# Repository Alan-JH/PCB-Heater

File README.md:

# PCB-Heater

Solder reflow hotplate design based on Carl Bugeja's idea and proof of concept.

Aluminum PCB as the resistive heating element, 200x200mm. Control board is separated and has displays for time and temperature (target and actual), and an SD card to read reflow profiles and save data to. Runs off of 3.3V logic and the ATTiny1614/1624 MCU. Input voltage (for the heating element) can range up to around 50V by design (Plan to use 36-48V), and the element itself should have a resistance of 5.1Ohm at 25C. Target maximum temperature is around 200C. Optional cooling provided by a 5V fan.

v1.0 results: 215C max temperature, 25 to 200C in around 4 minutes. 5 ohm resistance at room temperature, 10 ohm at 200C

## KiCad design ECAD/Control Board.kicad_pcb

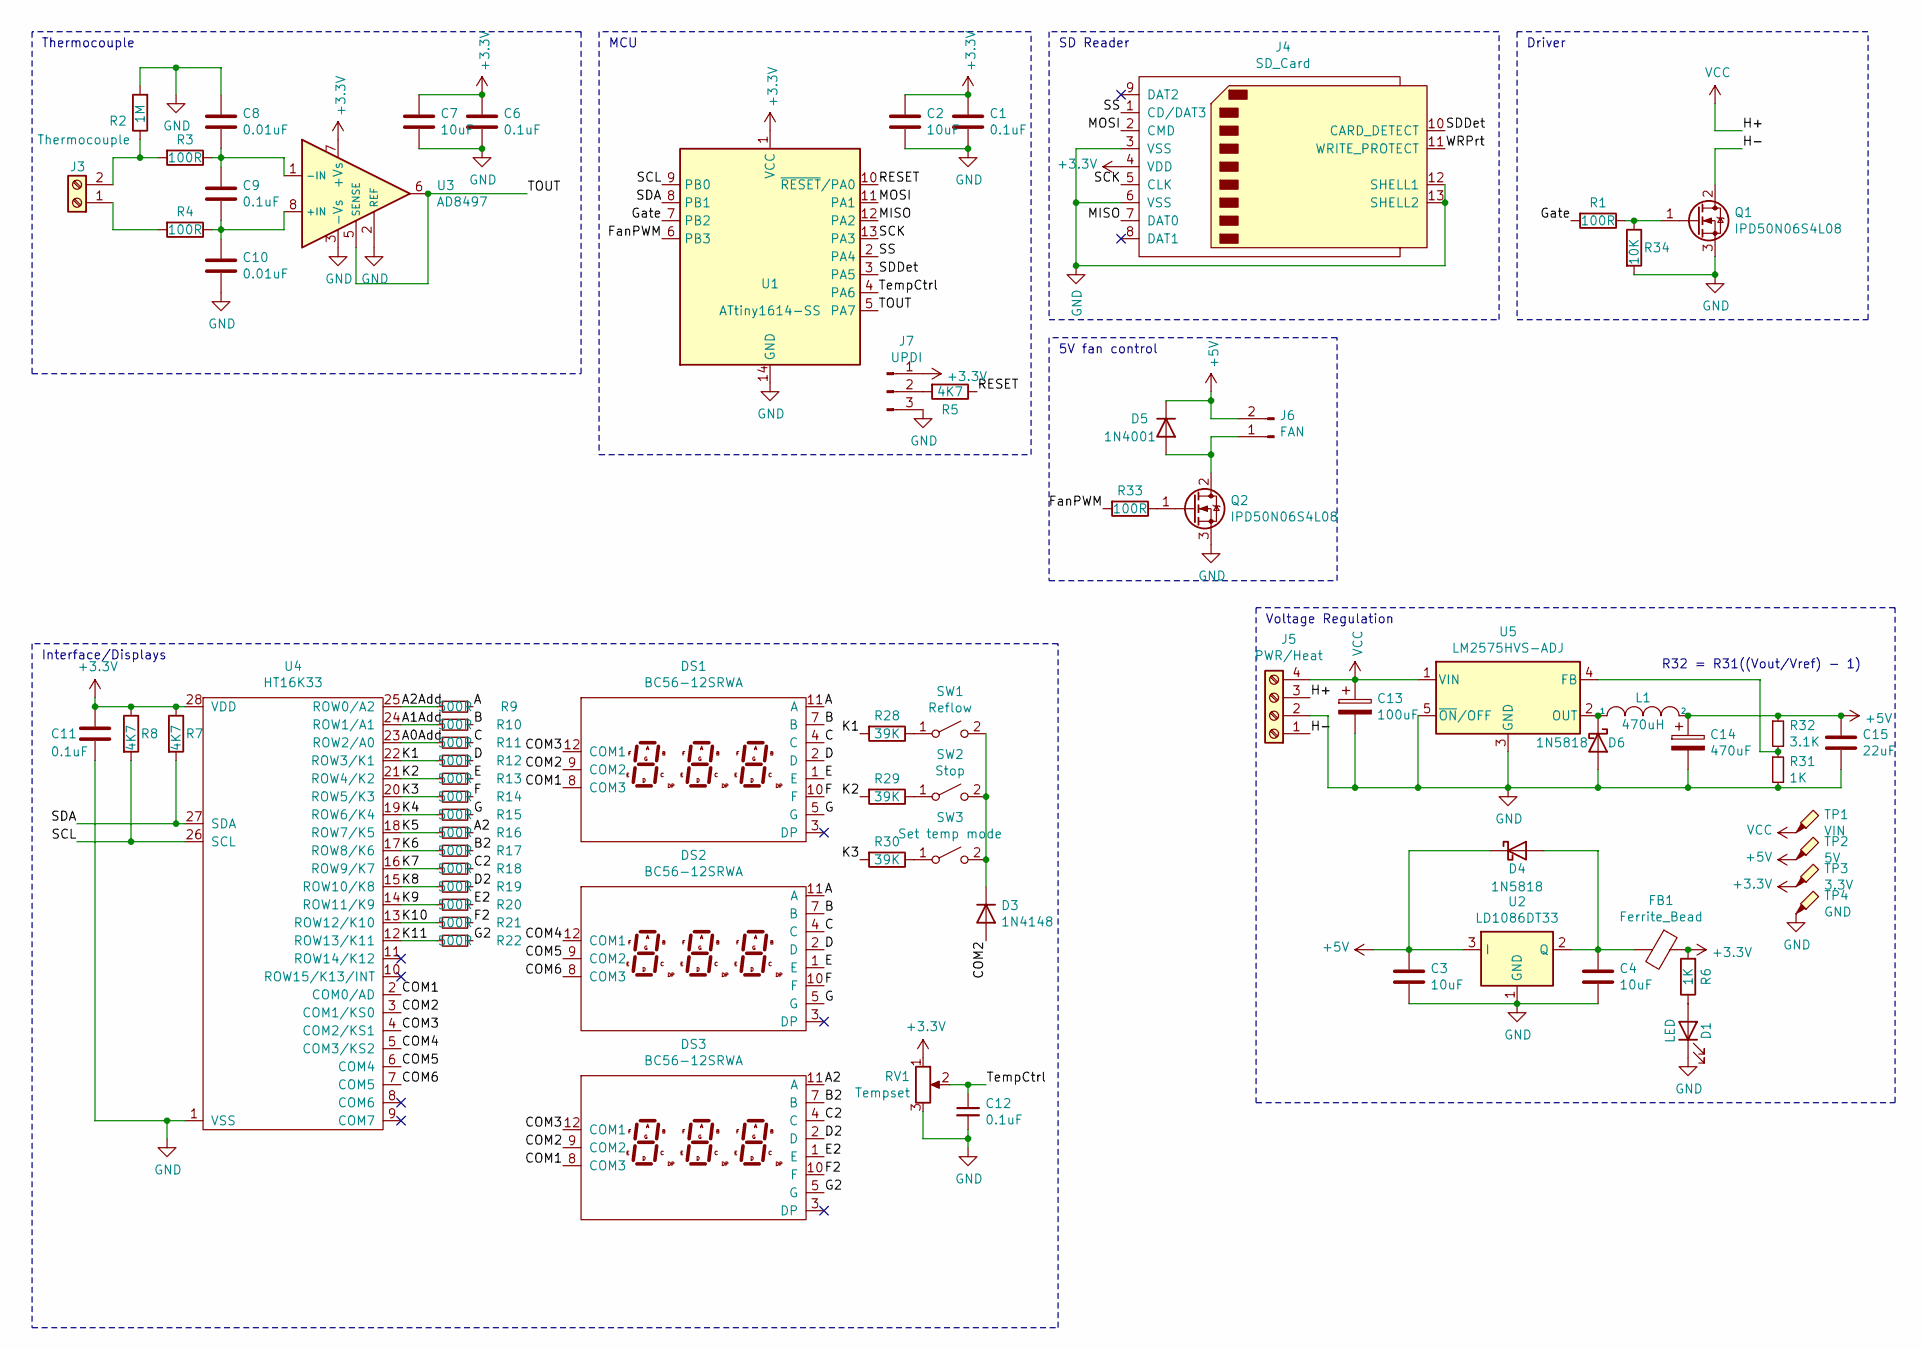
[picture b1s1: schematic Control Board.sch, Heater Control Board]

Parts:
C1, C6, C9, C11, C12: 0.1uF; C_0805_2012Metric_Pad1.18x1.45mm_HandSolder
C2, C3, C4, C7: 10uF; C_0805_2012Metric_Pad1.18x1.45mm_HandSolder
C8, C10: 0.01uF; C_0805_2012Metric_Pad1.18x1.45mm_HandSolder
C13: 100uF; CP_Elec_10x10.5
C14: 470uF; CP_Elec_8x10.5
C15: 22uF; C_0805_2012Metric_Pad1.18x1.45mm_HandSolder
D1: LED; LED_0805_2012Metric_Pad1.15x1.40mm_HandSolder
D3: 1N4148; D_0805_2012Metric_Pad1.15x1.40mm_HandSolder
D4, D6: 1N5818; D_T-1_P5.08mm_Horizontal
D5: 1N4001; D_T-1_P5.08mm_Horizontal
DS1, DS2, DS3: BC56-12SRWA
FB1: Ferrite_Bead; R_0805_2012Metric_Pad1.20x1.40mm_HandSolder
J3: Thermocouple; CUI-TB006-508-02BE
J4: SD_Card; SD_TE_2041021
J5: PWR/Heat; Molex-38711-2204
J6: FAN; PinHeader_1x02_P2.54mm_Vertical
J7: UPDI; PinHeader_1x03_P2.54mm_Vertical
L1: 470uH; L_12x12mm_H8mm
Q1, Q2: IPD50N06S4L08; TO-252-2
R1, R3, R4, R33: 100R; R_1206_3216Metric_Pad1.30x1.75mm_HandSolder
R2: 1M; R_1206_3216Metric_Pad1.30x1.75mm_HandSolder
R5, R7, R8: 4K7; R_1206_3216Metric_Pad1.30x1.75mm_HandSolder
R6: 1K; R_1206_3216Metric_Pad1.30x1.75mm_HandSolder
R9, R10, R11, R12, R13, R14, R15, R16, R17, R18, R19, R20, R21, R22: 500R; R_0805_2012Metric_Pad1.20x1.40mm_HandSolder
R28, R29, R30: 39K; R_1206_3216Metric_Pad1.30x1.75mm_HandSolder
R31: 1K; R_0805_2012Metric_Pad1.20x1.40mm_HandSolder
R32: 3.1K; R_0805_2012Metric_Pad1.20x1.40mm_HandSolder
R34: 10K; R_1206_3216Metric_Pad1.30x1.75mm_HandSolder
RV1: Tempset; PinHeader_1x03_P2.54mm_Vertical
SW1: Reflow; SW_PUSH_6mm_H7.3mm
SW2: Stop; SW_PUSH_6mm_H7.3mm
SW3: Set temp mode; SW_PUSH_6mm_H7.3mm
TP1: VIN; TestPoint_Pad_2.0x2.0mm
TP2: 5V; TestPoint_Pad_2.0x2.0mm
TP3: 3.3V; TestPoint_Pad_2.0x2.0mm
TP4: GND; TestPoint_Pad_2.0x2.0mm
U1: ATtiny1614-SS; SOIC-14_3.9x8.7mm_P1.27mm
U2: LD1086DT33; TO-252-3_TabPin2
U3: AD8497; MSOP-8_3x3mm_P0.65mm
U4: HT16K33; Holtek-HT16K33-SOP28-0
U5: LM2575HVS-ADJ; TO-263-5_TabPin3

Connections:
+3V3: C1.1, C2.1, C6.1, C7.1, C11.1, FB1.1, J4.4 (VDD), J7.1, R6.2, R7.1, R8.1, RV1.1, TP3.1, U1.1 (VCC), U3.7 (+Vs), U4.28 (VDD)
+5V: C3.1, C14.1, C15.1, D4.1 (K), D5.1 (K), J6.2, L1.2, R32.1, TP2.1, U2.3 (I)
/A: DS1.11 (A), DS2.11 (A), R9.1
/A0Add: R11.2, U4.23 (ROW2/A0)
/A1Add: R10.2, U4.24 (ROW1/A1)
/A2: DS3.11 (A), R16.1
/A2Add: R9.2, U4.25 (ROW0/A2)
/B: DS1.7 (B), DS2.7 (B), R10.1
/B2: DS3.7 (B), R17.1
/C: DS1.4 (C), DS2.4 (C), R11.1
/C2: DS3.4 (C), R18.1
/COM1: DS1.8 (COM3), DS3.8 (COM3), U4.2 (COM0/AD)
/COM2: D3.2 (A), DS1.9 (COM2), DS3.9 (COM2), U4.3 (COM1/KS0)
/COM3: DS1.12 (COM1), DS3.12 (COM1), U4.4 (COM2/KS1)
/COM4: DS2.12 (COM1), U4.5 (COM3/KS2)
/COM5: DS2.9 (COM2), U4.6 (COM4)
/COM6: DS2.8 (COM3), U4.7 (COM5)
/D: DS1.2 (D), DS2.2 (D), R12.1
/D2: DS3.2 (D), R19.1
/E: DS1.1 (E), DS2.1 (E), R13.1
/E2: DS3.1 (E), R20.1
/F: DS1.10 (F), DS2.10 (F), R14.1
/F2: DS3.10 (F), R21.1
/FanPWM: R33.2, U1.6 (PB3)
/G: DS1.5 (G), DS2.5 (G), R15.1
/G2: DS3.5 (G), R22.1
/Gate: R1.2, U1.7 (PB2)
/H-: J5.1, Q1.2 (D)
/K1: R12.2, R28.2, U4.22 (ROW3/K1)
/K2: R13.2, R29.2, U4.21 (ROW4/K2)
/K3: R14.2, R30.2, U4.20 (ROW5/K3)
/K4: R15.2, U4.19 (ROW6/K4)
/K5: R16.2, U4.18 (ROW7/K5)
/K6: R17.2, U4.17 (ROW8/K6)
/K7: R18.2, U4.16 (ROW9/K7)
/K8: R19.2, U4.15 (ROW10/K8)
/K9: R20.2, U4.14 (ROW11/K9)
/K10: R21.2, U4.13 (ROW12/K10)
/K11: R22.2, U4.12 (ROW13/K11)
/MISO: J4.7 (DAT0), U1.12 (PA2)
/MOSI: J4.2 (CMD), U1.11 (PA1)
/RESET: R5.1, U1.10 (~RESET~/PA0)
/SCK: J4.5 (CLK), U1.13 (PA3)
/SCL: R8.2, U1.9 (PB0), U4.26 (SCL)
/SDA: R7.2, U1.8 (PB1), U4.27 (SDA)
/SDDet: J4.10 (CARD_DETECT), U1.3 (PA5)
/SS: J4.1 (CD/DAT3), U1.2 (PA4)
/TOUT: U1.5 (PA7), U3.5 (SENSE), U3.6
/TempCtrl: C12.1, RV1.2, U1.4 (PA6)
GND: C1.2, C2.2, C3.2, C4.2, C6.2, C7.2, C8.1, C10.2, C11.2, C12.2, C13.2, C14.2, C15.2, D1.1 (K), D6.2 (A), J4.3 (VSS), J4.6 (VSS), J4.12 (SHELL1), J4.13 (SHELL2), J5.2, J7.3, Q1.3 (S), Q2.3 (S), R2.2, R31.2, R34.2, RV1.3, TP4.1, U1.14 (GND), U2.1 (GND), U3.2 (REF), U3.3 (-Vs), U4.1 (VSS), U5.3 (GND), U5.5 (~ON~/OFF)
unnamed: C4.1, D4.2 (A), FB1.2, U2.2 (Q)
unnamed: C8.2, C9.1, R3.1, U3.1 (-IN)
unnamed: C9.2, C10.1, R4.1, U3.8 (+IN)
unnamed: D1.2 (A), R6.1
unnamed: D3.1 (K), SW1.2 (B), SW2.2 (B), SW3.2 (B)
unnamed: D5.2 (A), J6.1, Q2.2 (D)
unnamed: D6.1 (K), L1.1, U5.2 (OUT)
unnamed: J3.1, R4.2
unnamed: J3.2, R2.1, R3.2
unnamed: J7.2, R5.2
unnamed: Q1.1 (G), R1.1, R34.1
unnamed: Q2.1 (G), R33.1
unnamed: R28.1, SW1.1 (A)
unnamed: R29.1, SW2.1 (A)
unnamed: R30.1, SW3.1 (A)
unnamed: R31.1, R32.2, U5.4 (FB)
VCC: C13.1, J5.3, J5.4, TP1.1, U5.1 (VIN)

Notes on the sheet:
Thermocouple
Driver
SD Reader
Interface/Displays
MCU
5V fan control
R32 = R31((Vout/Vref) - 1)
Voltage Regulation

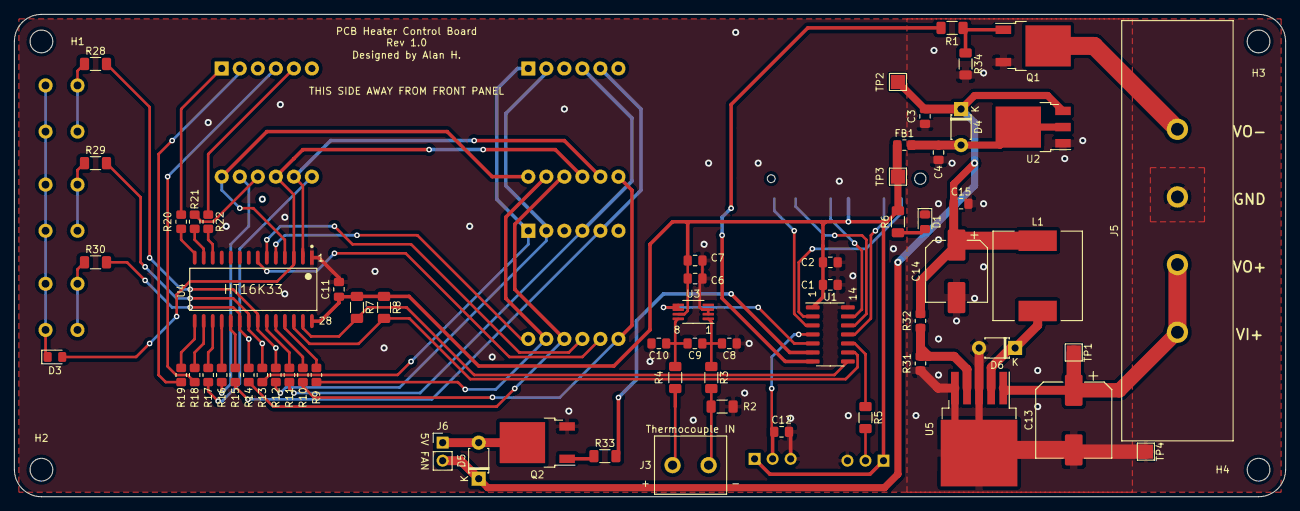
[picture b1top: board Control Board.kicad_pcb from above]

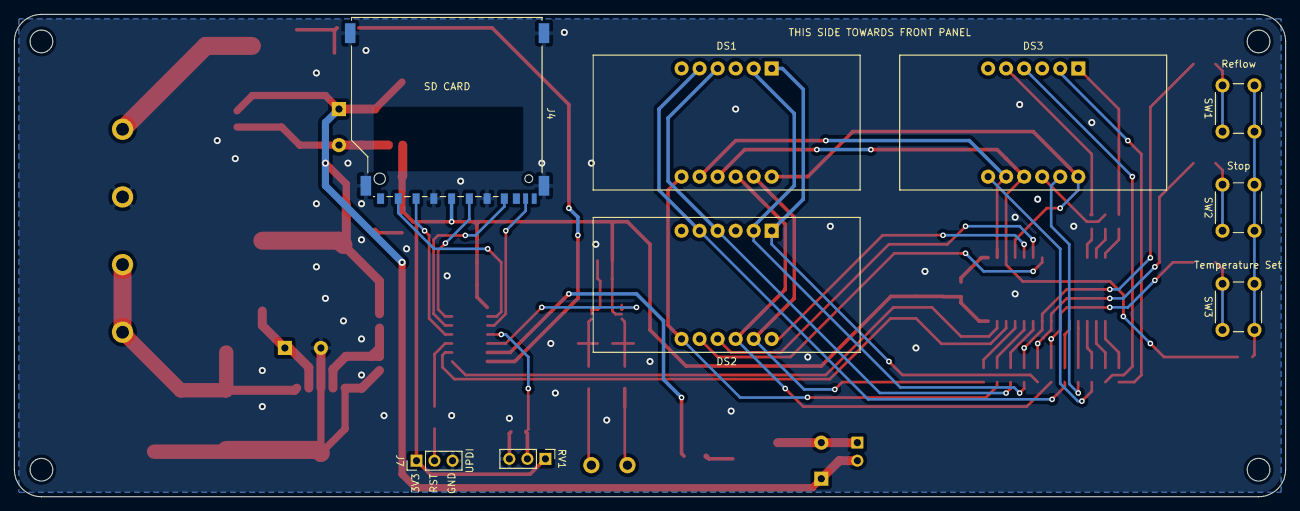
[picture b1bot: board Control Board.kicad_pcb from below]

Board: 2 copper layers, 179.1 x 67.9 mm, 77 parts (9 on the bottom side), 67 nets.

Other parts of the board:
H1, H2, H3, H4: MountingHole_3.2mm_M3

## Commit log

2021-09-07 Cleanup
    Renamed files, removed temp files
2021-09-07 Re-associated libraries
2021-09-07 Perforate Heatbed
    Added a grid of 2.1mm holes, which may help thermal performance.
2021-09-09 Widened traces to 30mil
    In order to reduce resistance and increase wattage, traces widened up to 30mil (theoretical 5.4R at 25C)
2021-09-09 High voltage modifications
    Widened high voltage tracks and replaced schottky diode with higher back voltage diode.
2021-09-10 Revised control board schematic
    Replaced single LDO setup with cascaded LDOs, so that a higher input voltage can be used, and the intermediate 12V can be used to power a fan. Added the appropriate circuitry to control a fan. Added 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
    Layout is still to be updated
2021-09-10 Added footprints to board
2021-09-10 Revert "Perforated heater"
2021-09-10 Revert "Merge pull request #3 from Alan-JH/revert-2-Perforated-Heater"
    This reverts commit 4dedab5329d0c4c589ebeff6f2ce44676f29a142, reversing
    changes made to 18337d37710a704d8d57a7691b9b75f48685949f.
2021-09-10 Update heater silkscreen info
2021-09-11 Re-arrange components
2021-09-11 Added pulldown to mosfet gate
2021-09-13 Replaced primary LDO with LM317
2021-09-14 Replaced linear regulator with switching regulator
    Chose switching regulator for the sake of less heat. Undecided as to whether I will end up using a premade module or incorporating the circuitry
    Replaced 12V rail with 5V rail, to increase efficiency of the LDO. Requires a 5V fan now.
    Bumped revision number to 0.4
2021-09-14 Remove extra LC filter, replace with ceramic cap
2021-09-15 Associate footprints and update board
2021-09-16 Lay out switching regulator
    Also reshuffling the SD card and power port placements
2021-09-16 More routing
2021-09-19 Routed V0.4 Control Board
    Finished routing board, removed ununsed models and footprints, re-exported gerbers and .STEP files
2021-09-20 BOM Export, minor via edits and gerber re-export
2021-10-08 start fixing errors in board
2021-10-09 Finish rerouting LDO
2021-10-10 Fix major silkscreen error, push to rev0.5
2021-10-11 Fix thermocouple + and - pins
2021-10-12 Firmware: implement PID
2021-10-12 Widen heater tracks
    reduce actual resistance from 7ohm to 5ohm
2021-10-12 attempt to fix pid
2021-10-12 clean up code
2021-10-12 more comments in firmware
2021-10-12 firmware
2021-10-12 tune pid
2021-10-24 Push v1.0 release version
